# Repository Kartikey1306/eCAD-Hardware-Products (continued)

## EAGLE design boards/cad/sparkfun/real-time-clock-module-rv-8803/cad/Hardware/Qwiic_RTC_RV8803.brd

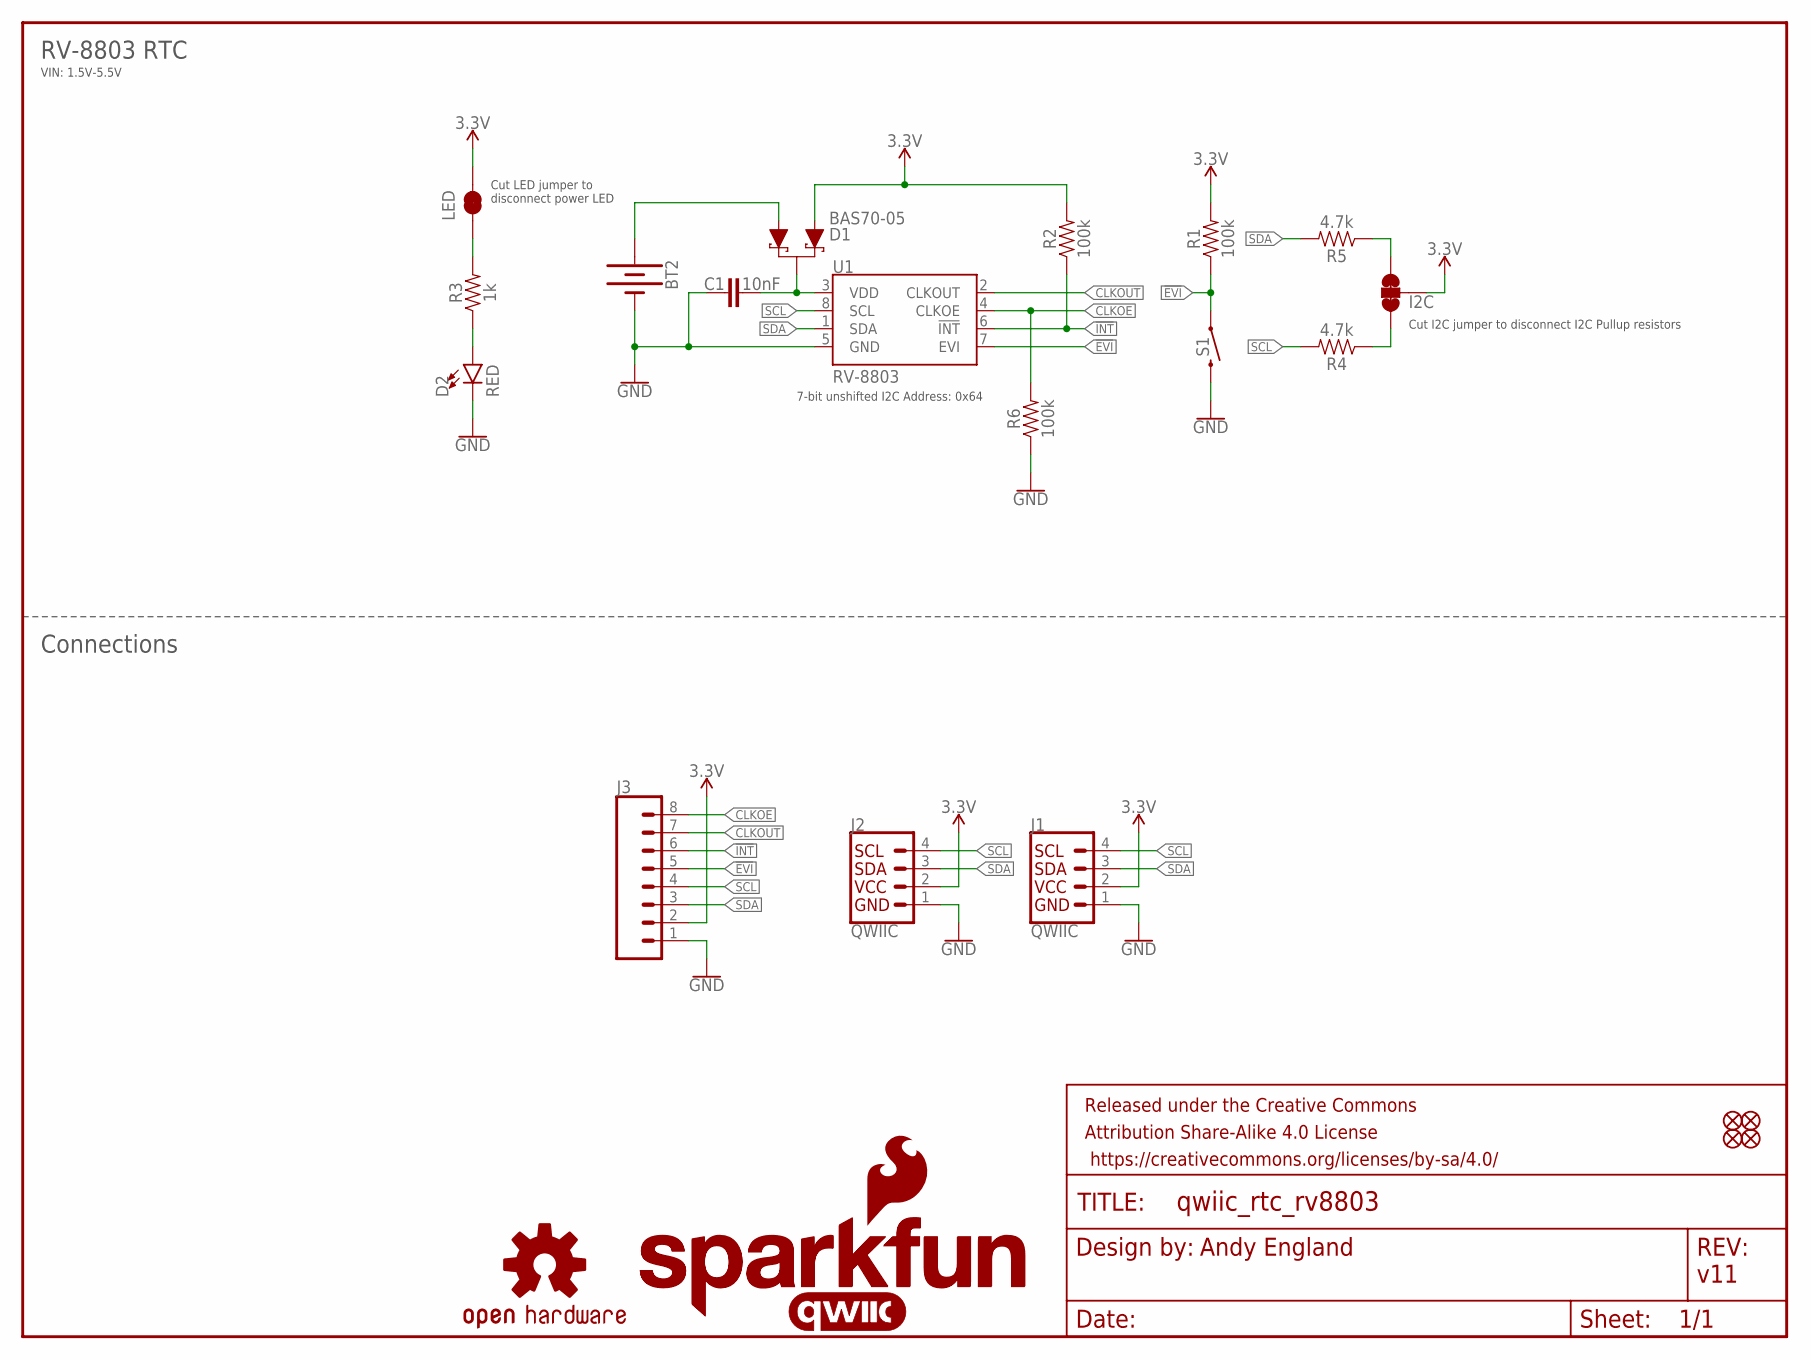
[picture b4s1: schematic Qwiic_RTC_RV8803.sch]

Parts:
BT2: BATTERY-12MM_SMD; BATTCON_12MM
C1: 10nF; 0603
D1: BAS70-05; SOT23-3
D2: RED; LED-0603
FD1, FD2, FD3, FD4: FIDUCIALUFIDUCIAL; FIDUCIAL-MICRO
FRAME1: FRAME-LETTER; CREATIVE_COMMONS
I2C: JUMPER-SMT_3_2-NC_TRACE_NO-SILK; SMT-JUMPER_3_2-NC_TRACE_NO-SILK
J1, J2: QWIIC; JST04_1MM_RA
J3: CONN_08NO_SILK_FEMALE_PTH; 1X08_NO_SILK
LED: JUMPER-SMT_2_NC_TRACE_NO-SILK; SMT-JUMPER_2_NC_TRACE_NO-SILK
LOGO1: SFE_LOGO_NAME_FLAME.1_INCH; SFE_LOGO_NAME_FLAME_.1
LOGO2: OSHW-LOGOS; OSHW-LOGO-S
LOGO4: QWIIC_LOGO_5MM; QWIIC_5MM
LOGO5: SFE_LOGO_NAME.1_INCH; SFE_LOGO_NAME_.1
R1, R2, R6: 100k; 0603
R3: 1k; 0603
R4, R5: 4.7k; 0603
S1: MOMENTARY-SWITCH-SPST-SMD-5.2MM-TALL; TACTILE_SWITCH_SMD_5.2MM
U1: RV-8803; RV-3028

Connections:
3.3V: D1.1 (A), I2C.2, J1.2, J2.2, J3.2, LED.2, R1.2, R2.2
!EVI: J3.5, R1.1, S1.1, U1.7 (EVI)
!INT: J3.6, R2.1, U1.6 (!INT)
CLKOE: J3.8, R6.2, U1.4 (CLKOE)
CLKOUT: J3.7, U1.2 (CLKOUT)
GND: BT2.GND (-), C1.1, D2.C, J1.1, J2.1, J3.1, R6.1, S1.3 (2), U1.5 (GND)
unnamed: C1.2, D1.3 (C), U1.3 (VDD)
unnamed: D2.A, R3.1
unnamed: BT2.PWR@1 (+), D1.2 (A1)
unnamed: LED.1, R3.2
unnamed: I2C.3, R5.1
unnamed: I2C.1, R4.1
SCL: J1.4, J2.4, J3.4, R4.2, U1.8 (SCL)
SDA: J1.3, J2.3, J3.3, R5.2, U1.1 (SDA)

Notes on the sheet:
Andy England
v11
Connections
RV-8803 RTC
VIN: 1.5V-5.5V
Cut I2C jumper to disconnect I2C Pullup resistors
Cut LED jumper to disconnect power LED
7-bit unshifted I2C Address: 0x64

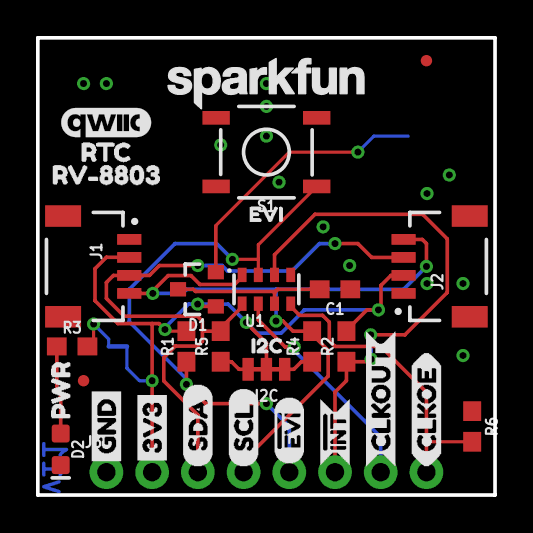
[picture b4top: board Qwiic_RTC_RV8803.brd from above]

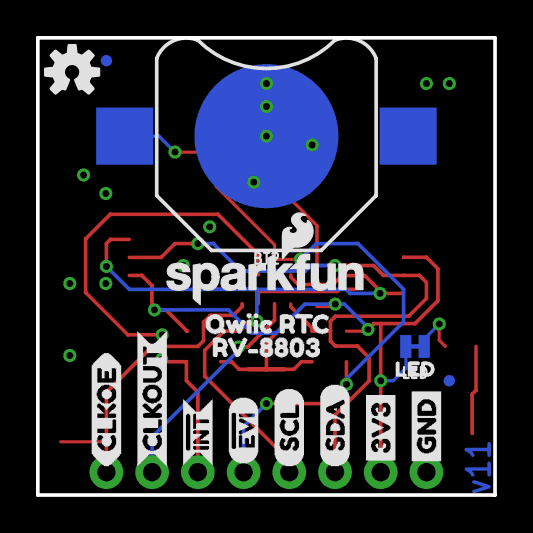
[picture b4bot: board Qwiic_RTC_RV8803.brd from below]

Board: 2 copper layers, 25.4 x 25.4 mm, 50 parts (17 on the bottom side), 14 nets.

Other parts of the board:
U$1, U$2: 3V31
U$3, U$4: GND0
U$5, U$6: SDA2
U$7, U$8: SCL3
U$9, U$10: #EVI2
U$11, U$12: CLKOUT6
U$13, U$14: CLKOE7
U$15, U$16: #INT5
U$17: PWR7
U$18: EVI1
U$19: I2C0
U$20: LED2
U$21: QWIIC_RTC0
U$22, U$24: _RV#88031
U$25: RTC0
